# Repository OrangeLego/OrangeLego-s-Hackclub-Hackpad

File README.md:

This Hackpad is a 6 key macropad with a rotary encoder, and makes use of KMK firmware.

Features:

    3D Squirted Case (Many color choices, still don't know what I'll choose)
    EC11 Rotary encoder, as a volume knob and an audio ouput device switcher
    6 Keys, there purpose, up to you!
    KISS, Keep it simple silly(of course /s)

CAD Model:

Everything fits together using 5 M3 Bolts and heatset inserts. 4 for the case, one for the PCB.

It has 2 separate printed pieces. The base where the PCB sits and the top cover.

Made in Fusion360.

PCB

Here's the PCB. It was made in KiCad.

Firmware Overview

This hackpad uses KMK firmware for everything.

    the rotary encoder changes volume. press to caudio ouput device
    The 4 keys currently act as macros I change often.

BOM:

Here should be everything you need to make this hackpad

    6x Cherry MX Switches
    6x DSA Keycaps
    5x M3x5x4 Heatset inserts
    5x M3x16mm SHCS Bolts
    1x EC11 Rotary Encoder
    1x XIAO RP2040
    1x Case (2 printed parts)

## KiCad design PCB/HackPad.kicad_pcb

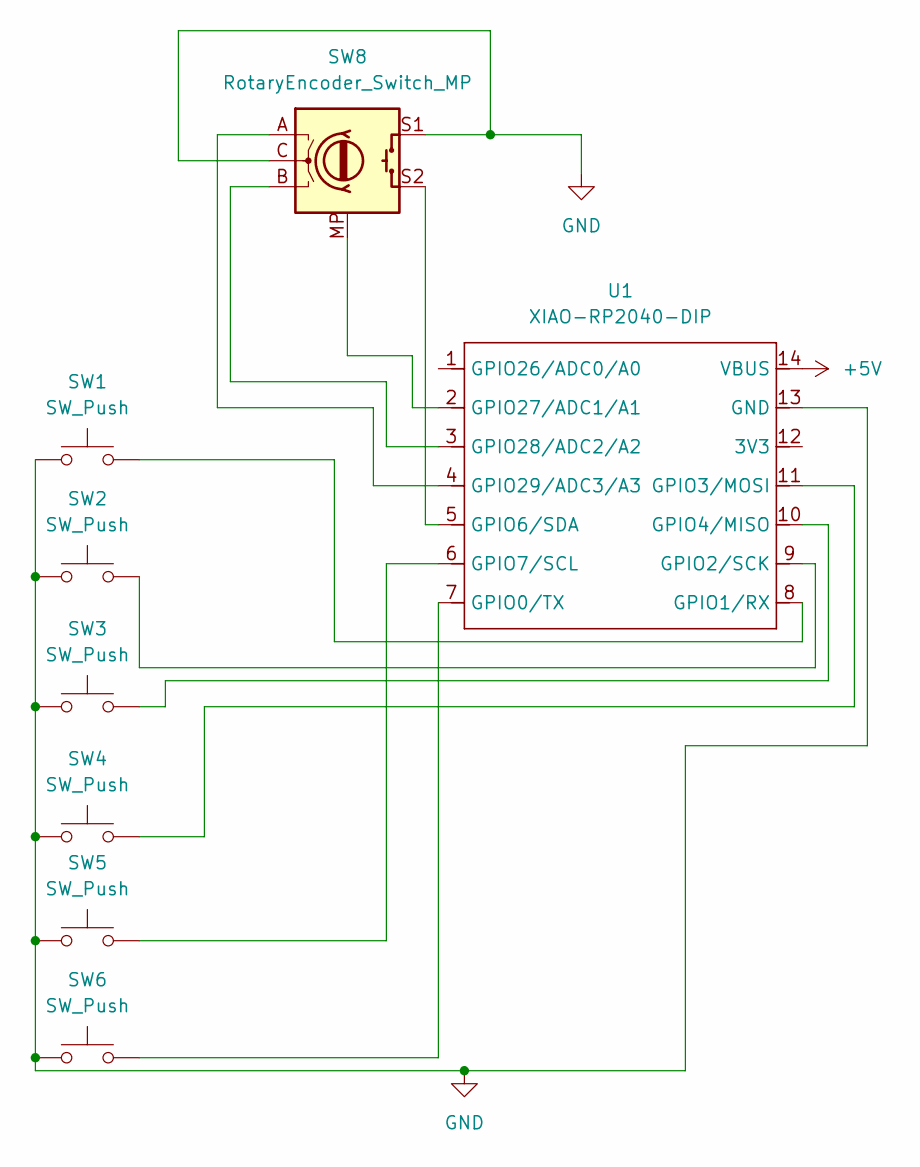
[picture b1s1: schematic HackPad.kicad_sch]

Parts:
SW1, SW2, SW3, SW4, SW5, SW6: SW_Push; SW_Cherry_MX_1.00u_PCB
SW8: RotaryEncoder_Switch_MP; RotaryEncoder_Alps_EC11E-Switch_Vertical_H20mm_CircularMoun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
U1: XIAO-RP2040-DIP

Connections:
+5V: U1.14 (VBUS)
GND: SW1.1, SW2.1, SW3.1, SW4.1, SW5.1, SW6.1, SW8.C, SW8.S1, U1.13 (GND)
unnamed: SW6.2, U1.7 (GPIO0/TX)
unnamed: SW1.2, U1.8 (GPIO1/RX)
unnamed: SW2.2, U1.9 (GPIO2/SCK)
unnamed: SW4.2, U1.11 (GPIO3/MOSI)
unnamed: SW3.2, U1.10 (GPIO4/MISO)
unnamed: SW8.S2, U1.5 (GPIO6/SDA)
unnamed: SW5.2, U1.6 (GPIO7/SCL)
unnamed: SW8.MP, U1.2 (GPIO27/ADC1/A1)
unnamed: SW8.B, U1.3 (GPIO28/ADC2/A2)
unnamed: SW8.A, U1.4 (GPIO29/ADC3/A3)

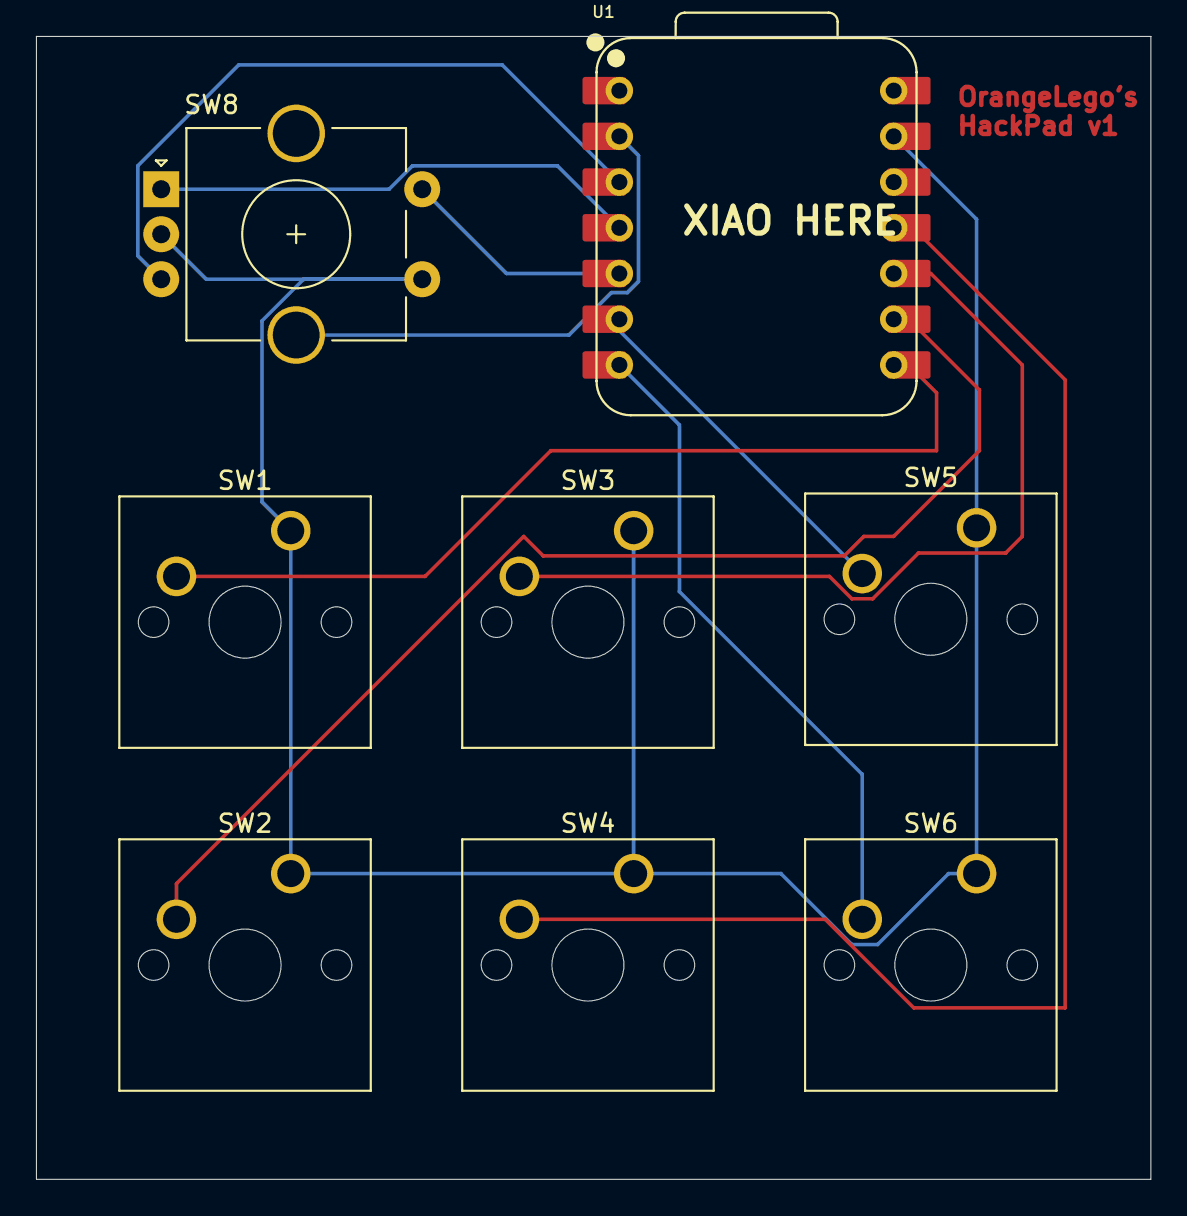
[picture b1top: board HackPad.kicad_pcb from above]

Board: 2 copper layers, 61.9 x 63.5 mm, 8 parts (0 on the bottom side), 11 nets.

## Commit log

2025-12-06 These are the initial case files
2025-12-06 Delete Step files directory
    Replacing it
2025-12-06 Standardized Acording to Hackclub
2026-04-08 Actual Firmware
2026-04-08 Actual CAD
